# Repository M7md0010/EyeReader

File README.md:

# EyeReader — Assistive Blink-to-Speech & Smart-Home Wearable

> A wearable eye-blink interface that translates eyelid gestures into spoken phrases and smart-home commands for individuals with paralysis or speech impairments.

**Authors:** Mohamed Sameh & Mohamed Elawady  
**License:** MIT

---

## Table of Contents

- [Project Overview](#project-overview)
- [2022 → 2026 Evolution](#2022--2026-evolution)
- [Hardware Specifications (2026 Remaster)](#hardware-specifications-2026-remaster)
- [Firmware Architecture (2026 Remaster)](#firmware-architecture-2026-remaster)
- [Repository Structure](#repository-structure)
- [Build & Production Files](#build--production-files)
- [Blink Code Reference](#blink-code-reference)
- [Getting Started](#getting-started)
- [License](#license)

---

## Project Overview

EyeReader is a wearable assistive device that decodes voluntary eye-blink patterns — measured via a Time-of-Flight proximity sensor — into a set of pre-programmed actions. In **Speaking Mode**, blink codes trigger audio playback of phrases such as *"I need to drink"* or *"Help!!"* through a DFPlayer Mini. In **Smart-Home Mode**, the same blink vocabulary toggles GPIO-controlled appliances (lights, fans, doors, AC, etc.).

The system comprises two units:

| Unit | Role |
|------|------|
| **Transmitter** | Glasses-mounted sensor module. Detects eyelid proximity, classifies blink duration via hardware interrupts, and transmits events over BLE. |
| **Receiver** | Bedside or wearable hub. Decodes blink sequences, drives audio playback, and controls smart-home relays. |

---

## 2022 → 2026 Evolution

This project was originally built in 2022 as a high-school engineering prototype and has since been remastered as a university-level Computer Engineering portfolio piece.

| Aspect | 2022 Prototype | 2026 Remaster |
|--------|---------------|---------------|
| **MCU** | 2× ESP32 DevKits (breadboarded) | Nordic nRF52840 SoC on a custom 4-layer HDI PCB |
| **Sensor** | Generic IR reflectance sensor | VL53L0X Time-of-Flight sensor over a flexible printed circuit (FPC) |
| **Wireless** | ESP-NOW (Wi-Fi based, high power) | Bluetooth Low Energy 5.0 (BLE) |
| **Antenna** | External PCB trace (hand-routed) | Standard built-in onboard zig-zag trace antenna (validated RF performance) |
| **Power Management** | USB-only, no battery | MCP73831 single-cell LiPo charger with integrated thermal regulation |
| **Haptic Driver** | Direct GPIO (no protection) | BSS138 N-Channel MOSFET + 1N4148 flyback diode motor driver |
| **Form Factor** | Breadboard + jumper wires (~120 × 80 mm) | 15 × 50 mm 4-layer HDI PCB |
| **Firmware Model** | Blocking `while` loops with `delay()` calls | Event-driven FreeRTOS architecture with hardware interrupts |
| **Power Consumption** | ~80 mA continuous (Wi-Fi always on) | ~8 µA deep sleep (BLE advertising + `waitForEvent()`) |
| **Code** | Monolithic `.ino` sketches | Modular C++ with ISR-driven state machine and RTOS software timers |

> The original 2022 code and Fritzing circuit images are preserved in the [`/Archive_2022`](Archive_2022/) directory for reference.

---

## Hardware Specifications (2026 Remaster)

### PCB

- **Dimensions:** 15 × 50 mm, 4-layer HDI stack-up
- **Fabrication:** Standard JLCPCB/PCBWay-compatible Gerber output
- **Design Tool:** KiCad 8.x

### Core Components

| Component | Part Number | Function |
|-----------|-------------|----------|
| **SoC** | Nordic nRF52840 | ARM Cortex-M4F @ 64 MHz, BLE 5.0, 1 MB Flash, 256 KB RAM |
| **ToF Sensor** | VL53L0X (ST) | 940 nm VCSEL laser ranging, I²C, hardware interrupt on threshold crossing. Mounted on FPC for flexible glasses-frame routing. |
| **LiPo Charger** | MCP73831 (Microchip) | Single-cell Li-Ion/LiPo charge management, 500 mA programmable charge current, thermal regulation |
| **Haptic Driver** | BSS138 + 1N4148 | Low-side N-FET switch for ERM vibration motor with flyback protection diode |

### RF Design

The RF front-end utilizes the **standard built-in onboard zig-zag trace antenna** pattern routed on the PCB top layer. This antenna geometry is a well-characterized design for 2.4 GHz BLE applications and was selected for its compact footprint and proven radiation efficiency without requiring an external antenna or matching network. The design has been validated for reliable BLE communication at the target operating range.

### Power Architecture

```
USB-C → MCP73831 → LiPo Cell (3.7V)
                 ↘ LDO → nRF52840 (1.8V–3.3V)
                       → VL53L0X (2.8V via XSHUT gating)
```

- **Deep sleep current:** ~8 µA (nRF52840 System ON, RAM retained, BLE advertising at 244 ms interval)
- **Active sensing current:** ~12 mA (ToF continuous ranging at 50 ms period)

---

## Firmware Architecture (2026 Remaster)

The firmware has been completely re-architected from the original ESP32 blocking-loop design to an **event-driven RTOS model** on the nRF52840.

### Key Design Decisions

1. **Hardware Interrupt-Driven Sensing:**  
   The VL53L0X is configured with a programmable distance threshold. When the eyelid crosses this threshold, the sensor asserts its GPIO interrupt pin. An ISR (`tof_isr`) captures the timestamp on both edges — eliminating continuous polling and enabling the MCU to remain in deep sleep between blinks.

2. **FreeRTOS Software Timers for Haptics:**  
   Haptic feedback (vibration motor pulse on long blinks ≥ 1000 ms) is managed by a one-shot FreeRTOS `SoftwareTimer` rather than a blocking `delay()`. This keeps the main loop non-blocking and power-efficient.

3. **Dynamic Threshold Detection:**  
   The blink threshold (currently 20 mm) is designed to be dynamically calibrated via a button ISR (pin reserved, TODO in firmware). This accommodates per-user anatomical variation.

4. **BLE Notification Model:**  
   Blink duration is transmitted as a 32-bit unsigned integer via a BLE GATT characteristic with `NOTIFY` property. The receiver subscribes to notifications and processes blink codes asynchronously — no polling or request/response overhead.

5. **Ultra-Low Power Loop:**  
   After processing a blink event, the main loop calls `waitForEvent()` (ARM WFE instruction), immediately returning the CPU to deep sleep. The loop thread is also suspended at startup via `suspendLoop()`, ensuring zero idle power waste.

### Firmware Files

| File | Description |
|------|-------------|
| [`Firmware/Transmitter.cpp`](Firmware/Transmitter.cpp) | nRF52840 transmitter — ISR-driven blink detection, BLE GATT server, FreeRTOS haptic timer |
| [`Firmware/EyeReaderReciever.ino`](Firmware/EyeReaderReciever.ino) | ESP32 BLE client receiver — blink code decoder, DFPlayer audio, smart-home GPIO control |

---

## Repository Structure

```
EyeReader/
├── Hardware/              # KiCad 8.x project files (schematic, PCB, netlist)
│   ├── v1.0.kicad_pro
│   ├── v1.0.kicad_sch
│   ├── v1.0.kicad_pcb
│   └── ...
├── Firmware/              # nRF52840 + ESP32 BLE firmware (2026)
│   ├── Transmitter.cpp
│   └── EyeReaderReciever.ino
├── Docs/                  # Generated documentation (schematic PDFs, etc.)
├── Production/            # Manufacturing output (Gerbers, drill files)
├── Archive_2022/          # Original high-school prototype code & images
│   ├── EyeReaderTransmitter_ESP32.ino
│   ├── EyeReaderReciever_ESP32.ino
│   ├── Transmitter Circuit.jpg
│   └── Receiver Circuit.jpg
├── generate_production.sh # KiCad CLI export automation script
└── README.md              # This file
```

---

## Build & Production Files

### Automated Export Script

A bash script is provided to generate all manufacturing and documentation files from the KiCad project:

```bash
./generate_production.sh
```

This script uses the KiCad CLI to:
1. **Export schematic PDF** → `Docs/EyeReader_Schematic.pdf`
2. **Export Gerber files** → `Production/`
3. **Export drill files** → `Production/`

> **Prerequisites:** KiCad 8.x must be installed and `kicad-cli` available on `$PATH`.

---

## Blink Code Reference

Each blink is classified by duration:  
- `0` = Short blink (1–2 s)  
- `1` = Long blink (2–3 s)  
- `2` = End-of-sequence marker (0.5–1 s)  
- **Mode switch** = Very long blink (3–5 s)

### Speaking Mode

| Code | Phrase |
|------|--------|
| `0-0-2` | "I need to drink" |
| `0-1-2` | "I need to eat" |
| `1-0-0-2` | "I need to obey nature's call" |
| `1-1-0-2` | "Help!!" |
| `1-0-1-2` | "Hello" |
| `1-1-2` | "I am cold" |
| `1-1-1-2` | "Thanks" |
| `0-1-0-2` | "Give me a hug" |
| `0-0-1-2` | "I need to shower" |
| `0-0-0-2` | "I love you" |
| `0-1-1-2` | "Tell me a joke" |

### Smart-Home Mode

| Code | Action |
|------|--------|
| `0-0-2` | Toggle lamp |
| `0-1-2` | Toggle TV |
| `1-0-0-2` | Toggle fan |
| `1-1-0-2` | Open/close curtains |
| `1-0-1-2` | Open/close door |
| `1-1-2` | Toggle AC/heater |
| `1-1-1-2` | Read a book |
| `0-1-0-2` | Medication schedule |
| `0-0-1-2` | Monitor cameras |
| `0-0-0-2` | Make a call |
| `0-1-1-2` | Measure heart rate |

---

## Getting Started

### Hardware
1. Open the KiCad project from `Hardware/v1.0.kicad_pro`.
2. Review the schematic and PCB layout.
3. Run `./generate_production.sh` to generate Gerber and drill files for PCB fabrication.

### Firmware
1. **Transmitter (nRF52840):** Open `Firmware/Transmitter.cpp` in the Arduino IDE with the Adafruit nRF52 BSP installed. Select the `Adafruit Feather nRF52840` board (or your target) and upload.
2. **Receiver (ESP32):** Open `Firmware/EyeReaderReciever.ino` in the Arduino IDE with the ESP32 board package. Upload to the receiver ESP32.

### Dependencies
- [Adafruit nRF52 Arduino BSP](https://github.com/adafruit/Adafruit_nRF52_Arduino)
- [Adafruit VL53L0X Library](https://github.com/adafruit/Adafruit_VL53L0X)
- [DFRobotDFPlayerMini Library](https://github.com/DFRobot/DFRobotDFPlayerMini)

---

## License

This project is licensed under the MIT License — see the [LICENSE](LICENSE) file for details.

---

**Mohamed Sameh** · [GitHub](https://github.com/m7md0010)  
**Mohamed Elawady** · Co-Author

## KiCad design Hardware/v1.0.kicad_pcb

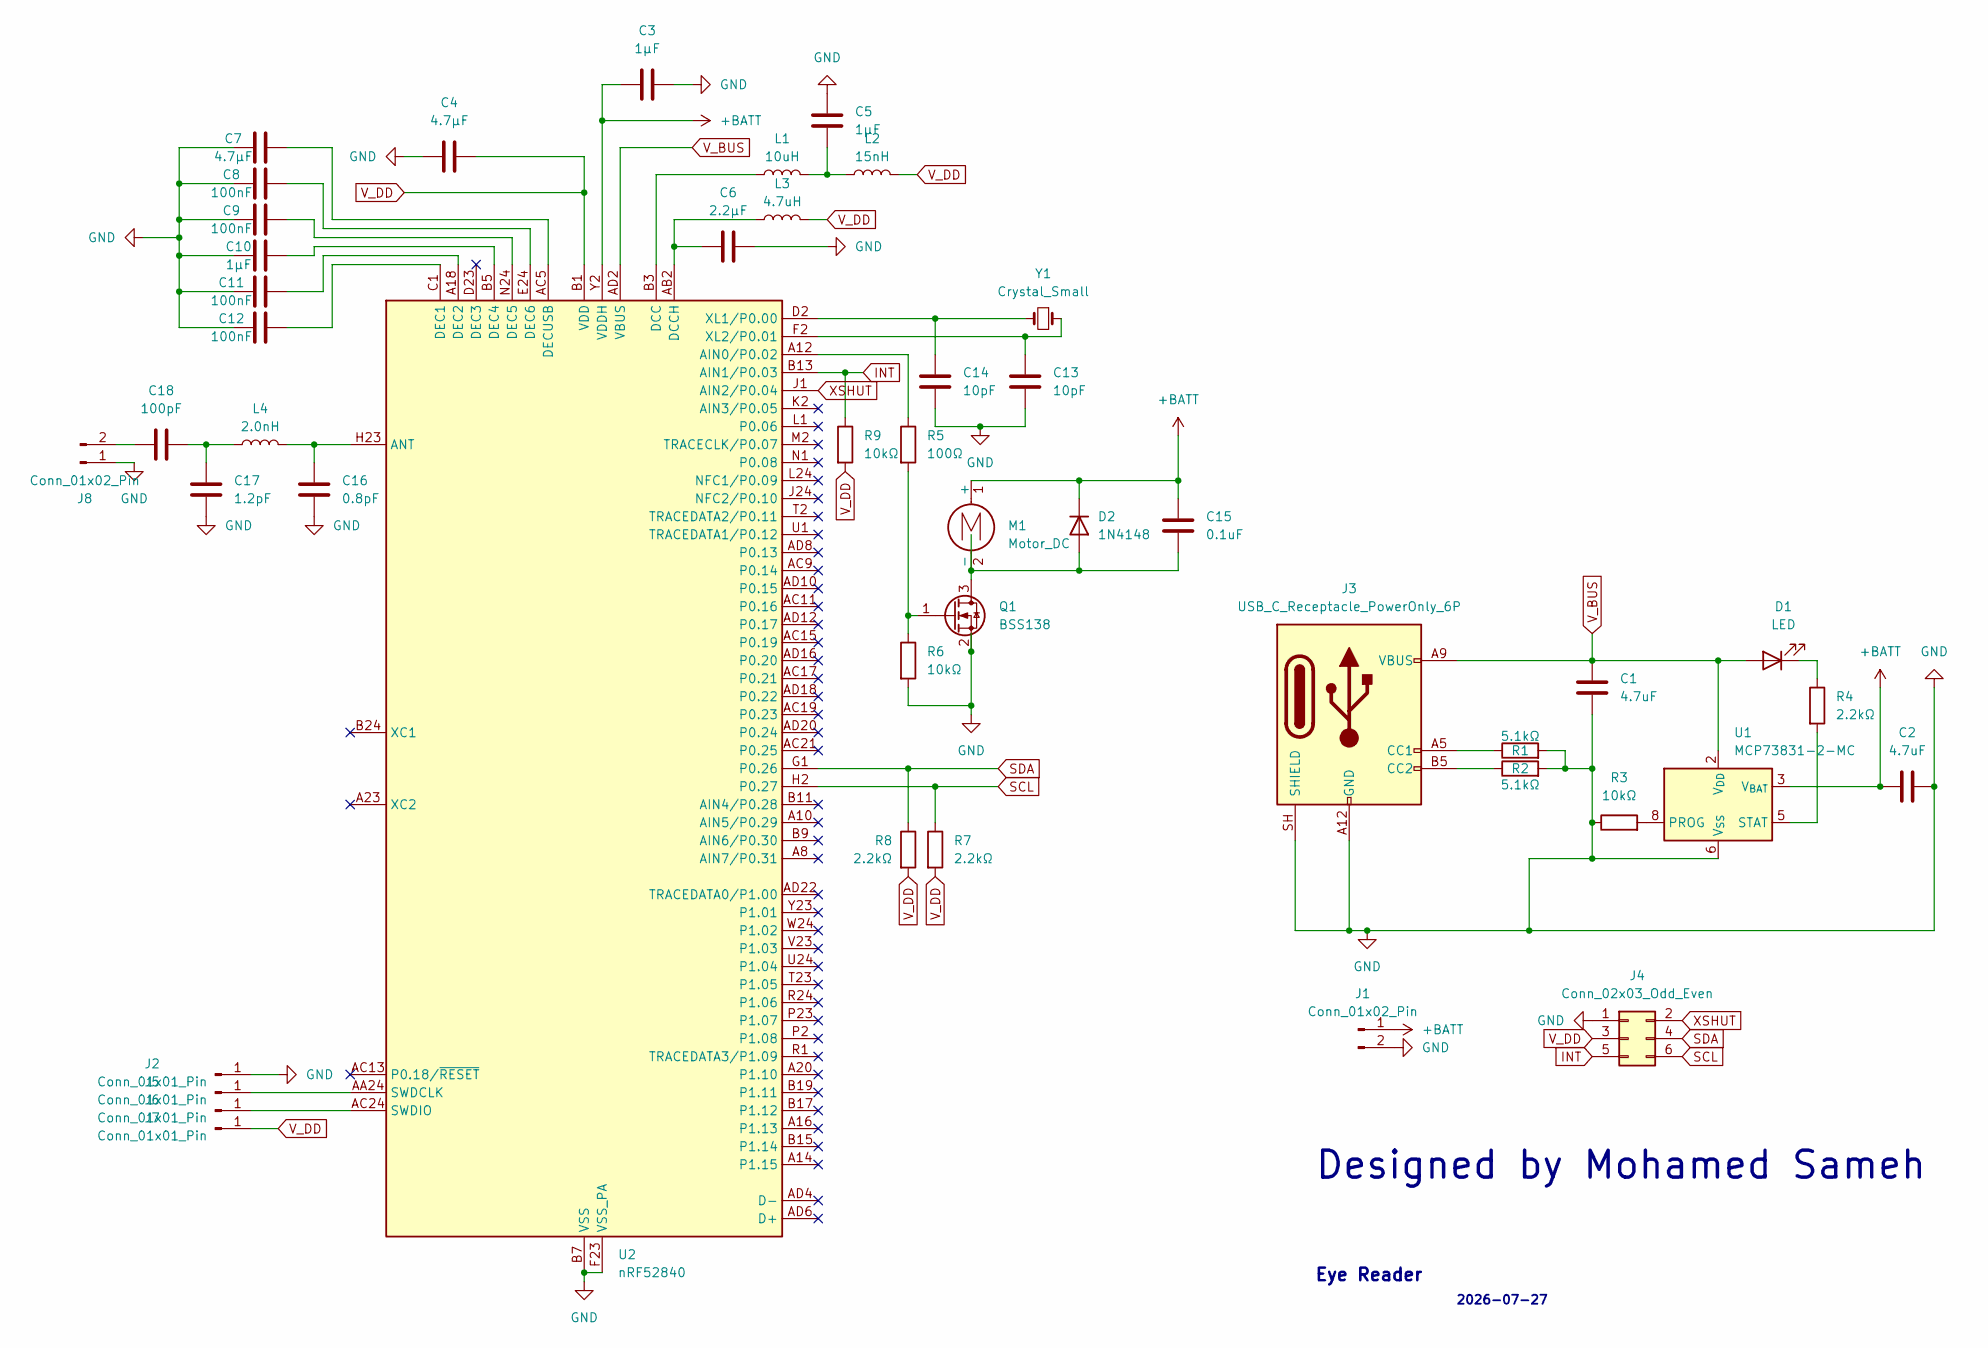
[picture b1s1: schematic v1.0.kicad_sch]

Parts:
C1, C2: 4.7uF; C_0402_1005Metric
C3, C5, C10: 1μF; C_0402_1005Metric
C4, C7: 4.7μF; C_0402_1005Metric
C6: 2.2μF; C_0402_1005Metric
C8, C9, C11, C12: 100nF; C_0402_1005Metric
C13, C14: 10pF; C_0402_1005Metric
C15: 0.1uF; C_0402_1005Metric
C16: 0.8pF; C_0402_1005Metric
C17: 1.2pF; C_0402_1005Metric
C18: 100pF; C_0402_1005Metric
D1: LED; LED_0603_1608Metric
D2: 1N4148; D_SOD-323
J1: Conn_01x02_Pin; JST_SH_SM02B-SRSS-TB_1x02-1MP_P1.00mm_Horizontal
J2, J5, J6, J7: Conn_01x01_Pin; TestPoint_Pad_D1.0mm
J3: USB_C_Receptacle_PowerOnly_6P; USB_C_Receptacle_GCT_USB4135-GF-A_6P_TopMnt_Horizontal
J4: Conn_02x03_Odd_Even; Hirose_FH12-6S-0.5SH_1x06-1MP_P0.50mm_Horizontal
J8: Conn_01x02_Pin; Texas_SWRA117D_2.4GHz_Left
L1: 10uH; L_0402_1005Metric
L2: 15nH; L_0402_1005Metric
L3: 4.7uH; L_0402_1005Metric
L4: 2.0nH; L_0402_1005Metric
M1: Motor_DC; SolderWire-0.1sqmm_1x02_P3.6mm_D0.4mm_OD1mm
Q1: BSS138; SOT-23
R1, R2: 5.1kΩ; R_0402_1005Metric
R3, R6, R9: 10kΩ; R_0402_1005Metric
R4, R7, R8: 2.2kΩ; R_0402_1005Metric
R5: 100Ω; R_0402_1005Metric
U1: MCP73831-2-MC; DFN-8-1EP_3x2mm_P0.5mm_EP1.7x1.4mm
U2: nRF52840; Nordic_AQFN-73-1EP_7x7mm_P0.5mm
Y1: Crystal_Small; Crystal_SMD_3215-2Pin_3.2x1.5mm

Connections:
+BATT: C2.1, C3.2, C15.2, D2.1 (K), J1.1, M1.1 (+), U1.3 (V_{BAT}), U1.4 (V_{BAT}), U2.Y2 (VDDH)
GND: C1.2, C2.2, C3.1, C4.1, C5.2, C6.2, C7.2, C8.2, C9.2, C10.2, C11.2, C12.2, C13.1, C14.1, C16.1, C17.1, J1.2, J2.1 (Pin_1_1), J3.A12 (GND), J3.B12 (GND), J3.SH (SHIELD), J4.1, J8.1, Q1.2 (S), R1.2, R2.2, R3.1, R6.2, U1.6 (V_{SS}), U2.B7 (VSS), U2.EP (VSS), U2.F23 (VSS_PA); also elsewhere on the board
INT: J4.5, R9.1, U2.B13 (AIN1/P0.03)
unnamed: C5.1, L1.2, L2.1
unnamed: C17.2, C18.2, L4.1
unnamed: D1.1 (K), R4.1
unnamed: C15.1, D2.2 (A), M1.2 (-), Q1.3 (D)
unnamed: J3.A5 (CC1), R1.1
unnamed: J3.B5 (CC2), R2.1
unnamed: J5.1 (Pin_1_1), U2.AA24 (SWDCLK)
unnamed: J6.1 (Pin_1_1), U2.AC24 (SWDIO)
unnamed: C18.1, J8.2
unnamed: Q1.1 (G), R5.2, R6.1
unnamed: R3.2, U1.8 (PROG)
unnamed: R4.2, U1.5 (STAT)
unnamed: R5.1, U2.A12 (AIN0/P0.02)
unnamed: C16.2, L4.2, U2.H23 (ANT)
unnamed: L1.1, U2.B3 (DCC)
unnamed: C6.1, L3.1, U2.AB2 (DCCH)
unnamed: C12.1, U2.C1 (DEC1)
unnamed: C11.1, U2.A18 (DEC2)
unnamed: C10.1, U2.B5 (DEC4)
unnamed: C9.1, U2.N24 (DEC5)
unnamed: C8.1, U2.E24 (DEC6)
unnamed: C7.1, U2.AC5 (DECUSB)
unnamed: C14.2, U2.D2 (XL1/P0.00), Y1.2
unnamed: C13.2, U2.F2 (XL2/P0.01), Y1.1
SCL: J4.6, R7.1, U2.H2 (P0.27)
SDA: J4.4, R8.1, U2.G1 (P0.26)
V_BUS: C1.1, D1.2 (A), J3.A9 (VBUS), J3.B9 (VBUS), U1.1 (V_{DD}), U1.2 (V_{DD}), U2.AD2 (VBUS)
V_DD: C4.2, J4.3, J7.1 (Pin_1_1), L2.2, L3.2, R7.2, R8.2, R9.2, U2.A22 (VDD), U2.AD14 (VDD), U2.AD23 (VDD), U2.B1 (VDD), U2.W1 (VDD); also elsewhere on the board
XSHUT: J4.2, U2.J1 (AIN2/P0.04)

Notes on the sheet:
Designed by Mohamed Sameh
2026-07-27
Eye Reader

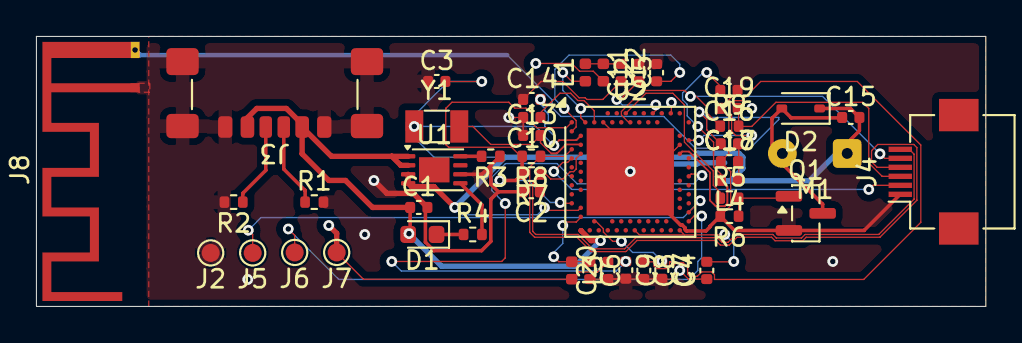
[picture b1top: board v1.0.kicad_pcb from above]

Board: 4 copper layers, 52.7 x 15.0 mm, 48 parts (1 on the bottom side), 32 nets.

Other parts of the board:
C19: 4.7uF; C_0402_1005Metric
C20: 100nF; C_0402_1005Metric

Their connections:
GND: C19.1, C20.1; also elsewhere on the board
V_DD: C19.2, C20.2; also elsewhere on the board

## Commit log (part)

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2025-06-30 Rename Reciver v6.0.jpg to Receiver Circuit.jpg
2025-06-30 Rename Transmitter v6.0.jpg to Transmitter Circuit.jpg
